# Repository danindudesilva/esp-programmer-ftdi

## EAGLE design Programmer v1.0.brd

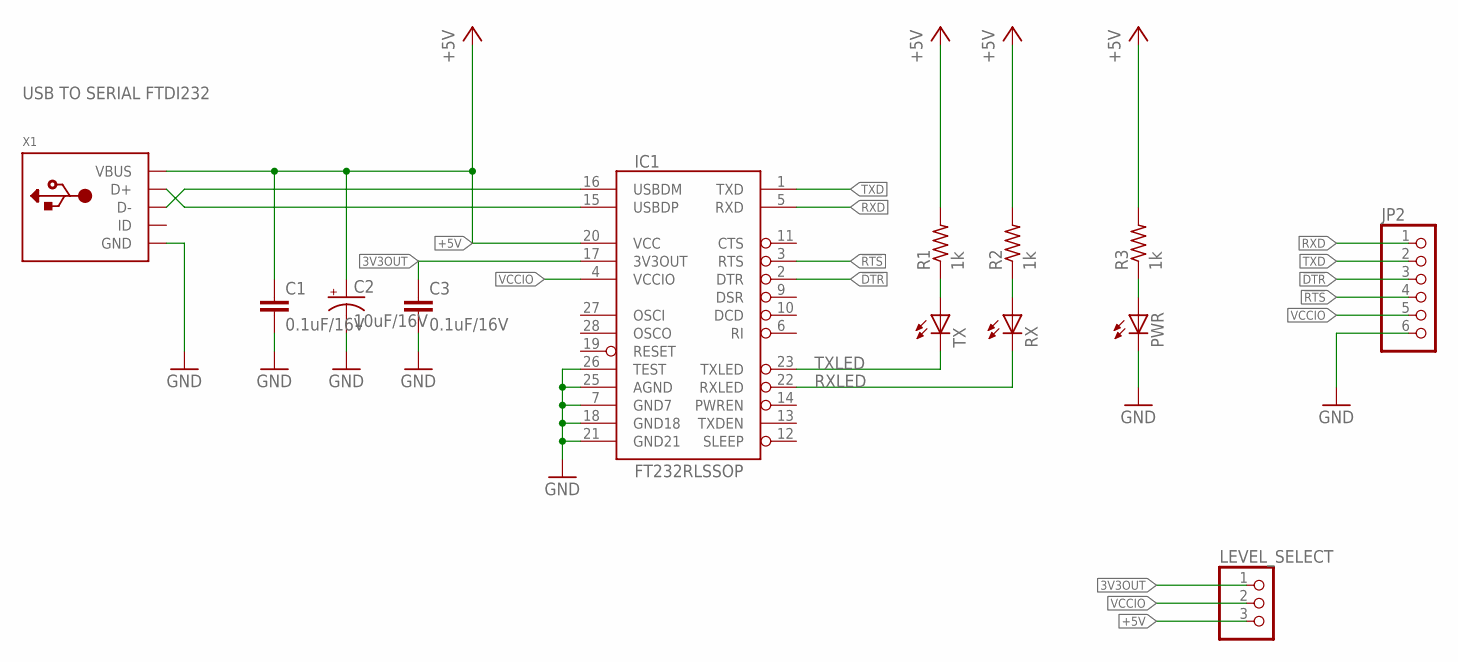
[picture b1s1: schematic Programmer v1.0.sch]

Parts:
C1, C3: 0.1uF/16V; C0805K
C2: 10uF/16V; SPARKFUN_EIA3216
IC1: FT232RLSSOP; SSOP28DB
JP2: PINHD-1X6; 1X06
LEVEL_SELECT: PINHD-1X3; 1X03
PWR: LEDCHIP-LED0805; CHIP-LED0805
R1, R2, R3: 1k; M0805
RX: LEDCHIP-LED0805; CHIP-LED0805
TX: LEDCHIP-LED0805; CHIP-LED0805
X1: USB_MICRO_20329_V2; 4UCONN_20329_V2

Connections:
3V3OUT: C3.1, IC1.17 (3V3OUT), LEVEL_SELECT.1
!DTR: IC1.2 (DTR), JP2.3
!RTS: IC1.3 (RTS), JP2.4
+5V: C1.1, C2.A (+), IC1.20 (VCC), LEVEL_SELECT.3, R1.2, R2.2, R3.2, X1.VBUS
GND: C1.2, C2.C (-), C3.2, IC1.7 (GND7), IC1.18 (GND18), IC1.21 (GND21), IC1.25 (AGND), IC1.26 (TEST), JP2.6, PWR.C, X1.BASE@1 (GND), X1.BASE@2 (GND), X1.GND, X1.SPRT@1 (GND), X1.SPRT@2 (GND), X1.SPRT@3 (GND), X1.SPRT@4 (GND)
unnamed: PWR.A, R3.1
unnamed: R1.1, TX.A
unnamed: R2.1, RX.A
RXD: IC1.5 (RXD), JP2.1
RXLED: IC1.22 (RXLED), RX.C
TXD: IC1.1 (TXD), JP2.2
TXLED: IC1.23 (TXLED), TX.C
USB_D+: IC1.15 (USBDP), X1.D+
USB_D-: IC1.16 (USBDM), X1.D-
VCCIO: IC1.4 (VCCIO), JP2.5, LEVEL_SELECT.2

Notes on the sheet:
USB TO SERIAL FTDI232

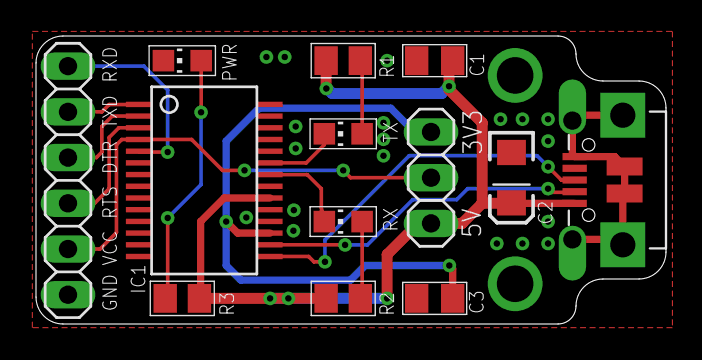
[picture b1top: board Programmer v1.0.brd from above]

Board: 2 copper layers, 35.0 x 16.0 mm, 13 parts (0 on the bottom side), 15 nets.
